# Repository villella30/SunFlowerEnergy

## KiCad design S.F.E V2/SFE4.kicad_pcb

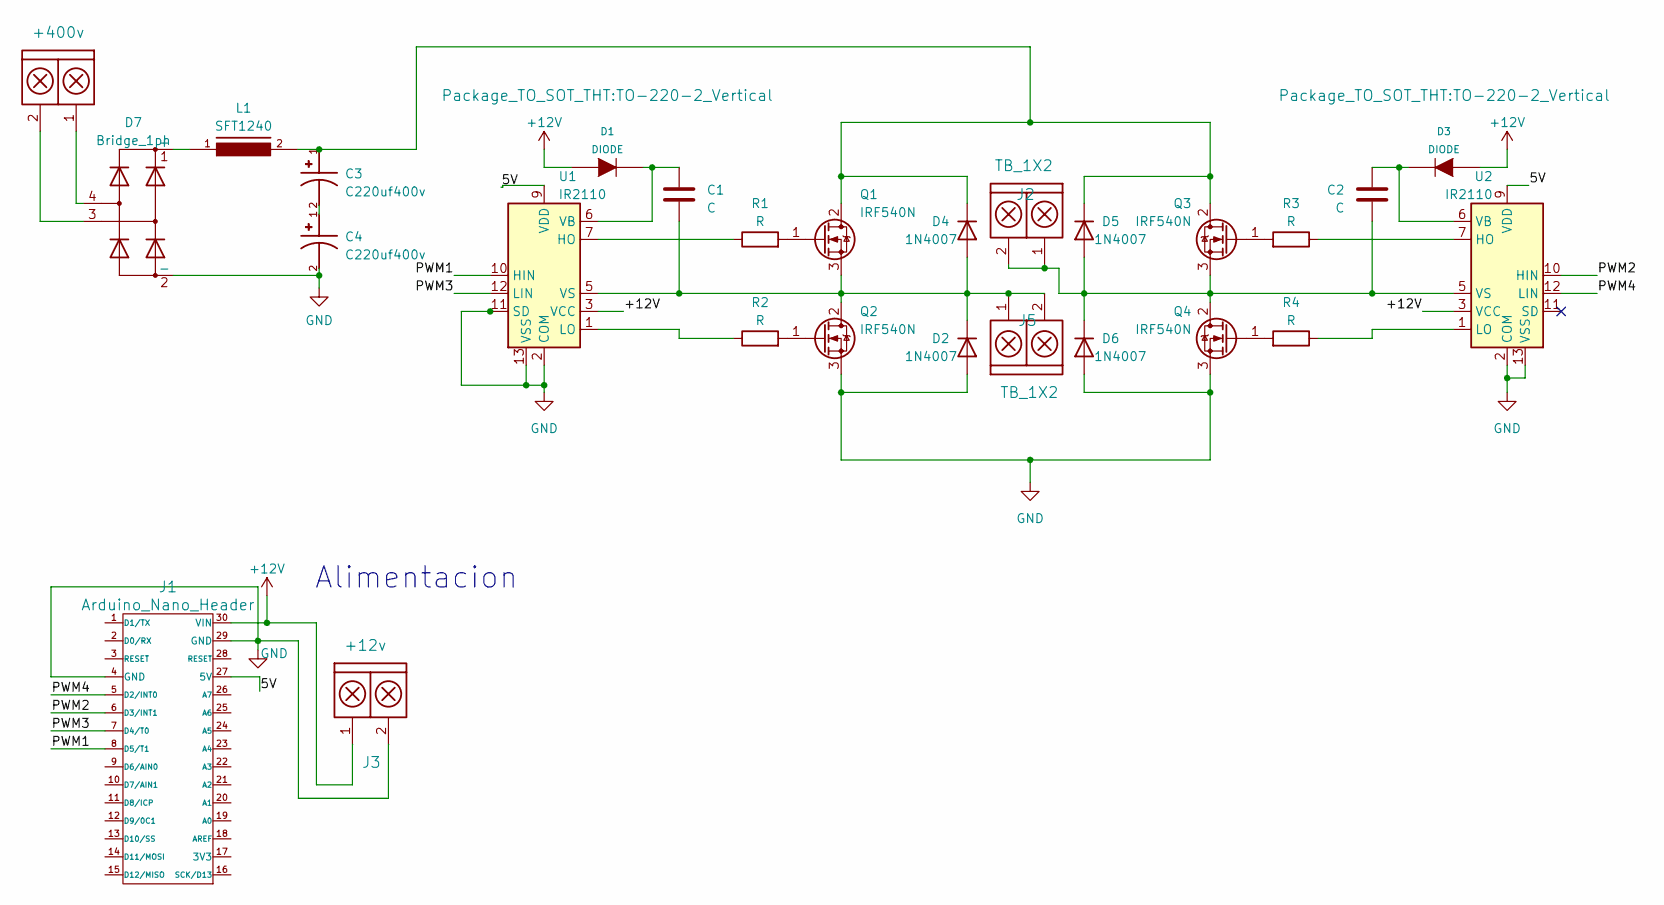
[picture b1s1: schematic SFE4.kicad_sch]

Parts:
C1, C2: C; C_Axial_L17.0mm_D6.5mm_P20.00mm_Horizontal
C3, C4: C220uf400v; CAP_B43548B9227M060; PARTREV 2018-10
D1, D3: DIODE; TO-220-2_Vertical
D2, D4, D5, D6: 1N4007; D_DO-41_SOD81_P10.16mm_Horizontal
D7: Bridge_1ph; P73_KBP
J1: Arduino_Nano_Header; arduino_nano_header
J2, J5: TB_1X2; BORNERA2_AZUL
J3: +12v; BORNERA2_AZUL
J4: +400v; BORNERA2_AZUL
L1: SFT1240
Q1, Q2, Q3, Q4: IRF540N; TO-220-3_Vertical
R1, R2, R3, R4: R; R_Axial_DIN0207_L6.3mm_D2.5mm_P10.16mm_Horizontal
U1, U2: IR2110; DIP-14_W7.62mm

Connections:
+12V: D1.1 (A), D3.1 (A), J1.30 (VIN), J3.1, U1.3 (VCC), U2.3 (VCC)
/5V: J1.27 (5V), U1.9 (VDD), U2.9 (VDD)
/PWM1: J1.8 (D5/T1), U1.10 (HIN)
/PWM2: J1.6 (D3/INT1), U2.10 (HIN)
/PWM3: J1.7 (D4/T0), U1.12 (LIN)
/PWM4: J1.5 (D2/INT0), U2.12 (LIN)
GND: C4.2, D2.2 (A), D6.2 (A), D7.2 (-), J1.4 (GND), J1.29 (GND), J3.2, Q2.3 (S), Q4.3 (S), U1.2 (COM), U1.11 (SD), U1.13 (VSS), U2.2 (COM), U2.13 (VSS)
unnamed: C3.2, C4.1
unnamed: C1.1, D1.2 (K), U1.6 (VB)
unnamed: C1.2, D2.1 (K), D4.2 (A), J5.1, J5.2, Q1.3 (S), Q2.2 (D), U1.5 (VS)
unnamed: C2.1, D3.2 (K), U2.6 (VB)
unnamed: C3.1, D4.1 (K), D5.1 (K), L1.2, Q1.2 (D), Q3.2 (D)
unnamed: C2.2, D5.2 (A), D6.1 (K), J2.1, J2.2, Q3.3 (S), Q4.2 (D), U2.5 (VS)
unnamed: D7.1 (+), L1.1
unnamed: D7.3, J4.2
unnamed: D7.4, J4.1
unnamed: Q1.1 (G), R1.2
unnamed: Q2.1 (G), R2.2
unnamed: Q3.1 (G), R3.2
unnamed: Q4.1 (G), R4.2
unnamed: R1.1, U1.7 (HO)
unnamed: R2.1, U1.1 (LO)
unnamed: R3.1, U2.7 (HO)
unnamed: R4.1, U2.1 (LO)

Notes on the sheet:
Alimentacion

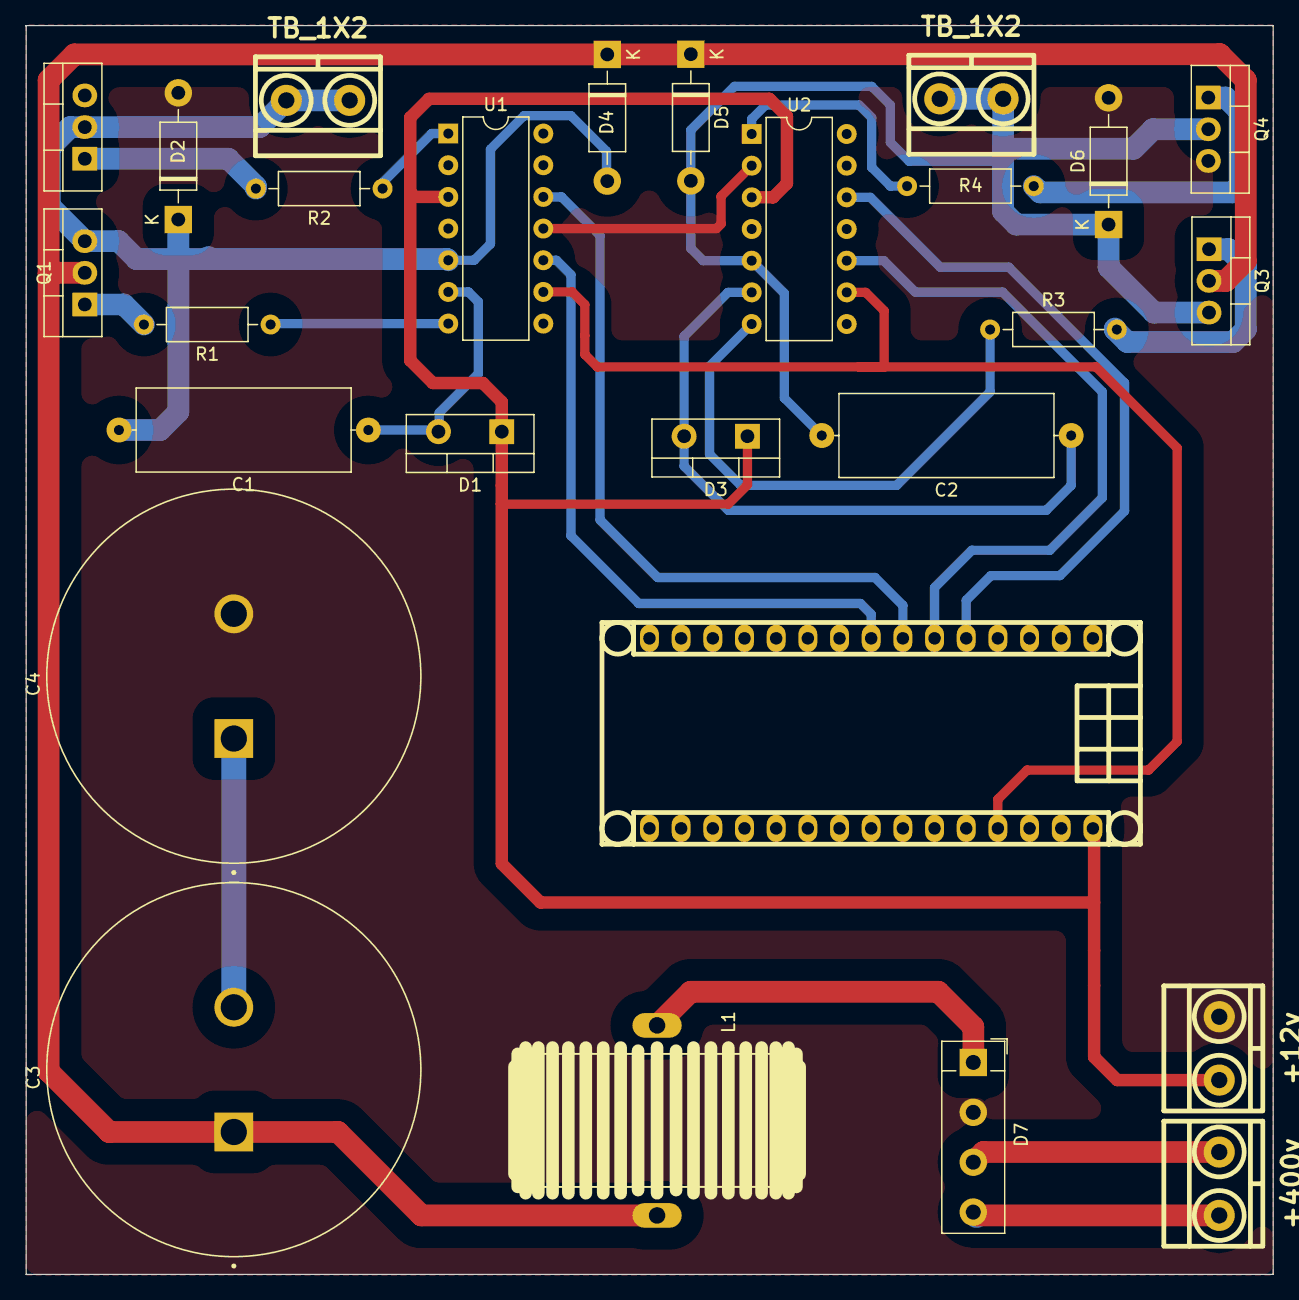
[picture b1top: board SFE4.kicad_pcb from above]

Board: 2 copper layers, 100.0 x 100.2 mm, 27 parts (0 on the bottom side), 24 nets.
